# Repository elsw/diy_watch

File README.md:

# binary_watch

This is a project to create a homecrew binary watch to fit inside a analogue wrist watch

## issues

- No Vcc out of the LTC4071 chip, swapped LBSEL to set the `Low Battery Connect` to 3.6V but never get any voltage out. Change to MCP73833? also cheaper. [reference curcuit](https://learn.adafruit.com/li-ion-and-lipoly-batteries/downloads)
- Cannot debug RP2040 code, got it working once but not again, I think it's something up with the cdoe itself, debugging reliable blink code though... (change to pico 2??) (try embassy???)

## TODO

- Swap battery charger for MCP73833 (C340160)
- Recreate breadboard setup, test in rust
- Change PCB to 4 layer
- Change programming port for 3 pin JST SH (pico probe standard)
- Romove bool sel switch in favour of solder pads
- Swap LIR battery with space for lipo
- Add charging state LED
- Swap RTC for PCF-8563 (C2651526)

## Components
```
Cheap 6 digit LCD display
Raspberry Pi RP2040 Microchip
150mah lipo - https://thepihut.com/products/150mah-3-7v-lipo-battery
DS3231 real time clock
charging chip (breakout https://www.adafruit.com/product/259)
Standarise programming port on pico probe wire (1mm JST-SH, SM03B-SRSS-TB)
```

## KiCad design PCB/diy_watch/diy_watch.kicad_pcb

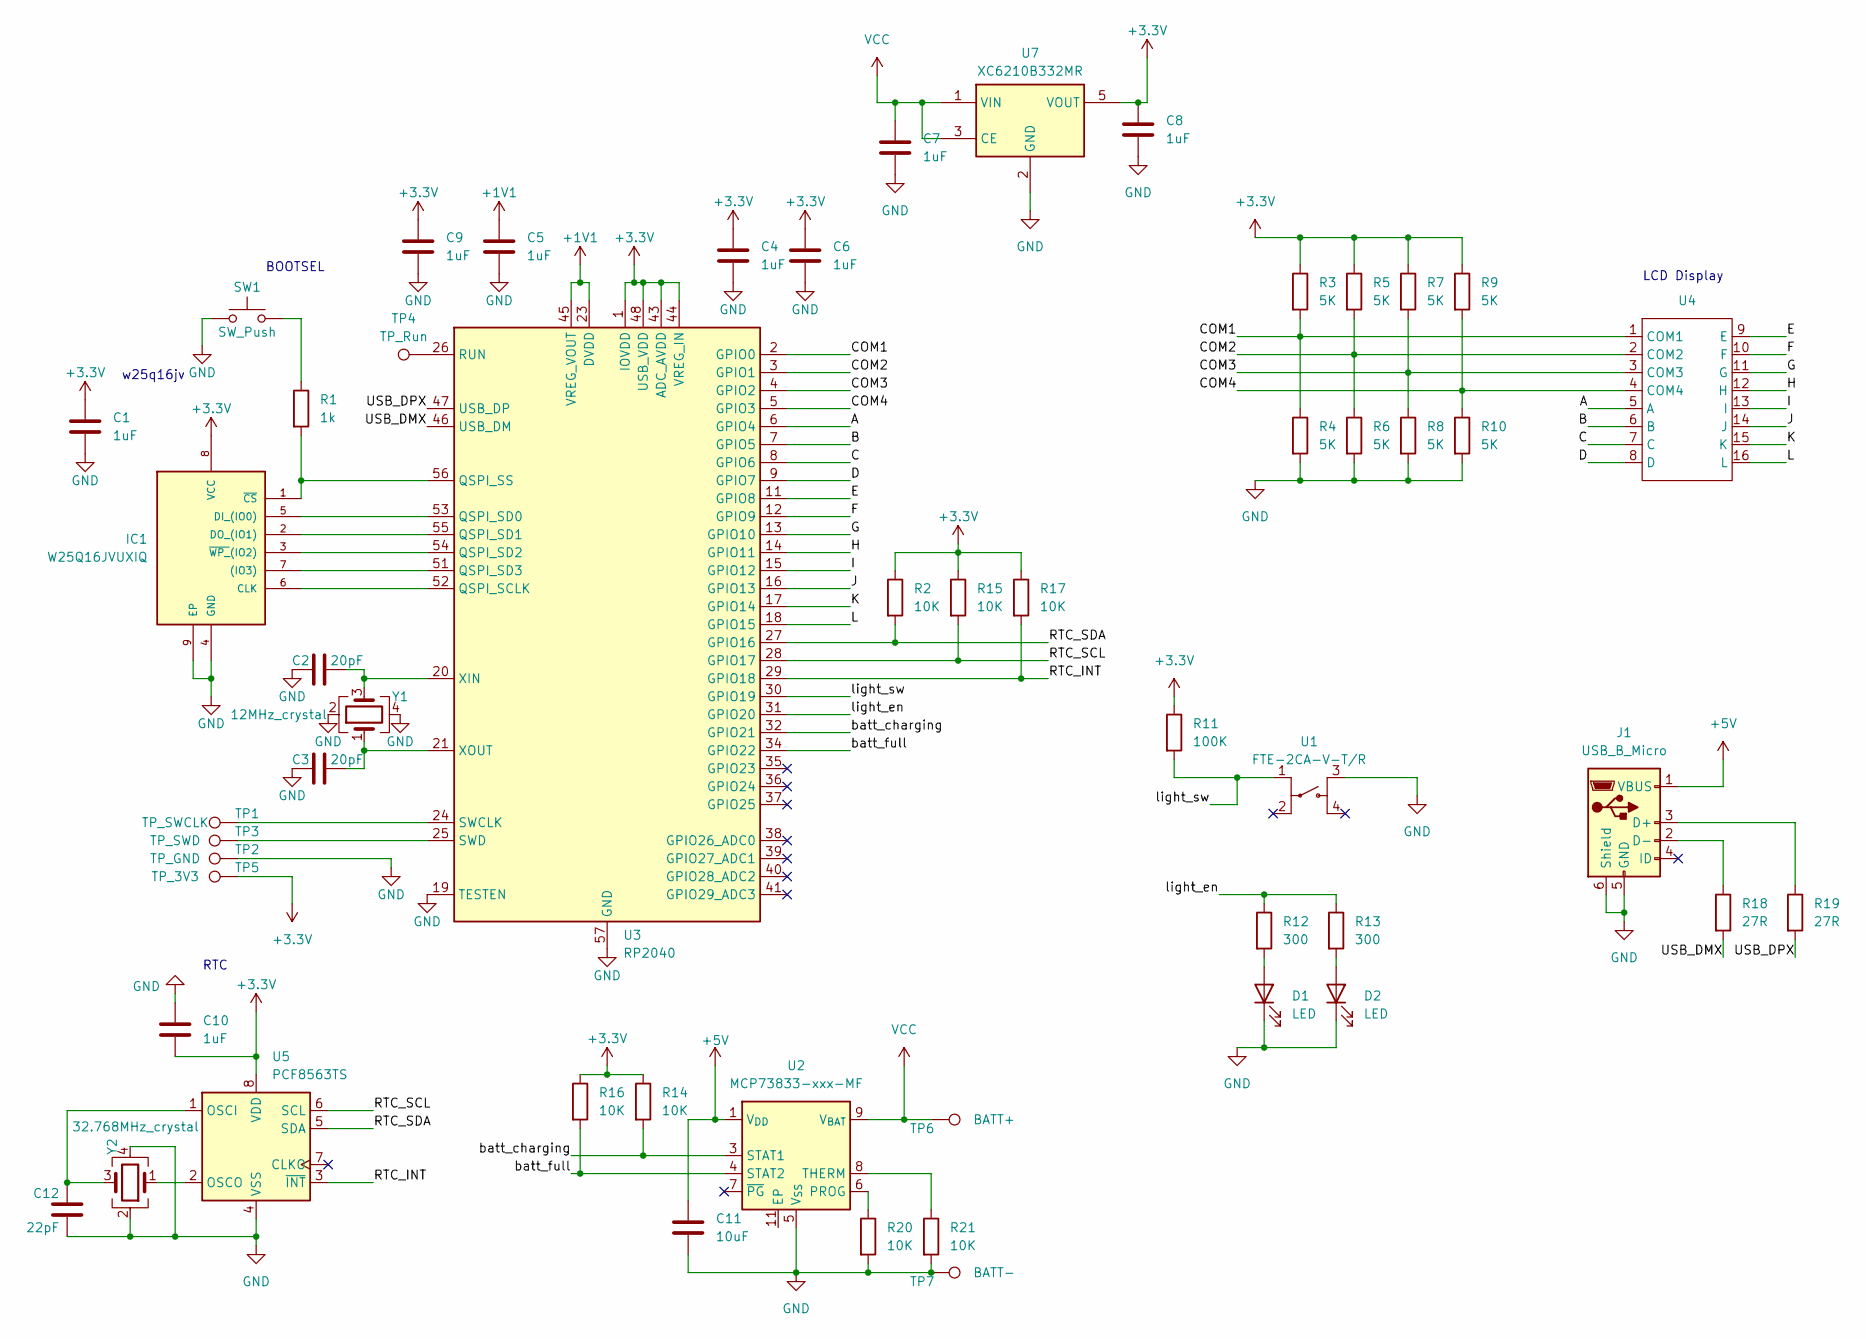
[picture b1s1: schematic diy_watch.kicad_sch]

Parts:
C1, C4, C5, C6, C7, C8, C9, C10: 1uF; C_0402_1005Metric; JLCPCB Part C52923
C2, C3: 20pF; C_0402_1005Metric; JLCPCB Part C1554
C11: 10uF; C_0402_1005Metric
C12: 22pF; C_0402_1005Metric
D1, D2: LED; LED_0805_2012Metric; JLCPCB Part C2296
IC1: W25Q16JVUXIQ; SON50P300X200X60-9N; MANUFACTURER_PART_NUMBER W25Q16JVUXIQ; JLCPCB Part C2843335
J1: USB_B_Micro; USB_Micro-B_GCT_USB3076-30-A
R1: 1k; R_0402_1005Metric; JLCPCB Part C11702
R2, R14, R15, R16, R17, R20, R21: 10K; R_0402_1005Metric; JLCPCB Part C25744
R3, R4, R5, R6, R7, R8, R9, R10: 5K; R_0402_1005Metric; JLCPCB Part C25900
R11: 100K; R_0402_1005Metric; JLCPCB Part C25741
R12: 300; R_0402_1005Metric; JLCPCB Part C25104
R13: 300; LED_0402_1005Metric; JLCPCB Part C25104
R18, R19: 27R; R_0402_1005Metric; JLCPCB Part C25100
SW1: SW_Push; SW_SPST_EVQP7C
TP1: TP_SWCLK; TestPoint_Pad_D1.5mm
TP2: TP_GND; TestPoint_Pad_D1.5mm
TP3: TP_SWD; TestPoint_Pad_D1.5mm
TP4: TP_Run; TestPoint_Pad_D1.0mm
TP5: TP_3V3; TestPoint_Pad_D1.5mm
TP6: BATT+; TestPoint_Pad_D1.5mm
TP7: BATT-; TestPoint_Pad_D1.5mm
U1: FTE-2CA-V-T/R; Diptronics FTE-3
U2: MCP73833-xxx-MF; DFN-10-1EP_3x3mm_P0.5mm_EP1.58x2.35mm
U3: RP2040; QFN-56-1EP_7x7mm_P0.4mm_EP3.2x3.2mm; JLCPCB Part C2040
U4: 6Dig7SegLCD
U5: PCF8563TS; MSOP-8_3x3mm_P0.65mm
U7: XC6210B332MR; SOT-23-5; JLCPCB Part C47719
Y1: 12MHz_crystal; Crystal_SMD_2520-4Pin_2.5x2.0mm; JLCPCB Part C252259
Y2: 32.768MHz_crystal; Crystal_SMD_2520-4Pin_2.5x2.0mm; JLCPCB Part C9002

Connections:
+1V1: C5.1, U3.23 (DVDD), U3.45 (VREG_VOUT), U3.50 (DVDD)
+3.3V: C1.1, C4.1, C6.1, C8.1, C9.1, C10.2, IC1.8 (VCC), R2.1, R3.1, R5.1, R7.1, R9.1, R11.1, R14.1, R15.1, R16.1, R17.1, TP5.1, U3.1 (IOVDD), U3.10 (IOVDD), U3.22 (IOVDD), U3.33 (IOVDD), U3.42 (IOVDD), U3.43 (ADC_AVDD), U3.44 (VREG_IN), U3.48 (USB_VDD), U3.49 (IOVDD), U5.8 (VDD), U7.5 (VOUT)
+5V: C11.1, J1.1 (VBUS), U2.1 (V_{DD}), U2.2 (V_{DD})
/A: U3.6 (GPIO4), U4.5 (A)
/B: U3.7 (GPIO5), U4.6 (B)
/C: U3.8 (GPIO6), U4.7 (C)
/COM1: R3.2, R4.1, U3.2 (GPIO0), U4.1 (COM1)
/COM2: R5.2, R6.1, U3.3 (GPIO1), U4.2 (COM2)
/COM3: R7.2, R8.1, U3.4 (GPIO2), U4.3 (COM3)
/COM4: R9.2, R10.1, U3.5 (GPIO3), U4.4 (COM4)
/D: U3.9 (GPIO7), U4.8 (D)
/E: U3.11 (GPIO8), U4.9 (E)
/F: U3.12 (GPIO9), U4.10 (F)
/G: U3.13 (GPIO10), U4.11 (G)
/H: U3.14 (GPIO11), U4.12 (H)
/I: U3.15 (GPIO12), U4.13 (I)
/J: U3.16 (GPIO13), U4.14 (J)
/K: U3.17 (GPIO14), U4.15 (K)
/L: U3.18 (GPIO15), U4.16 (L)
/RTC_INT: R17.2, U3.29 (GPIO18), U5.3 (~INT)
/RTC_SCL: R15.2, U3.28 (GPIO17), U5.6 (SCL)
/RTC_SDA: R2.2, U3.27 (GPIO16), U5.5 (SDA)
/USB_DMX: R18.2, U3.46 (USB_DM)
/USB_DPX: R19.2, U3.47 (USB_DP)
/batt_charging: R14.2, U2.3 (STAT1), U3.32 (GPIO21)
/batt_full: R16.2, U2.4 (STAT2), U3.34 (GPIO22)
/light_en: R12.1, R13.1, U3.31 (GPIO20)
/light_sw: R11.2, U1.1, U3.30 (GPIO19)
GND: C1.2, C2.1, C3.1, C4.2, C5.2, C6.2, C7.2, C8.2, C9.2, C10.1, C11.2, C12.1, D1.1 (K), D2.1 (K), IC1.4 (GND), IC1.9 (EP), J1.5 (GND), J1.6 (Shield), R4.2, R6.2, R8.2, R10.2, R20.2, R21.2, SW1.1, TP2.1, TP7.1, U1.3, U2.5 (V_{SS}), U3.19 (TESTEN), U3.57 (GND), U5.4 (VSS), U7.2 (GND), Y1.2, Y1.4, Y2.2, Y2.4
unnamed: D1.2 (A), R12.2
unnamed: D2.2 (A), R13.2
unnamed: IC1.7 ((IO3)), U3.51 (QSPI_SD3)
unnamed: IC1.6 (CLK), U3.52 (QSPI_SCLK)
unnamed: IC1.5 (DI_(IO0)), U3.53 (QSPI_SD0)
unnamed: IC1.2 (DO_(IO1)), U3.55 (QSPI_SD1)
unnamed: IC1.1 (~CS), R1.2, U3.56 (QSPI_SS)
unnamed: IC1.3 (~WP_(IO2)), U3.54 (QSPI_SD2)
unnamed: J1.3 (D+), R19.1
unnamed: J1.2 (D-), R18.1
unnamed: R1.1, SW1.2
unnamed: R20.1, U2.6 (PROG)
unnamed: R21.1, U2.8 (THERM)
unnamed: TP4.1, U3.26 (RUN)
unnamed: TP1.1, U3.24 (SWCLK)
unnamed: TP3.1, U3.25 (SWD)
unnamed: C2.2, U3.20 (XIN), Y1.3
unnamed: C3.2, U3.21 (XOUT), Y1.1
unnamed: C12.2, U5.1 (OSCI), Y2.3
unnamed: U5.2 (OSCO), Y2.1
VCC: C7.1, TP6.1, U2.9 (V_{BAT}), U2.10 (V_{BAT}), U7.1 (VIN), U7.3 (CE)

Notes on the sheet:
RTC
w25q16jv
BOOTSEL
LCD Display

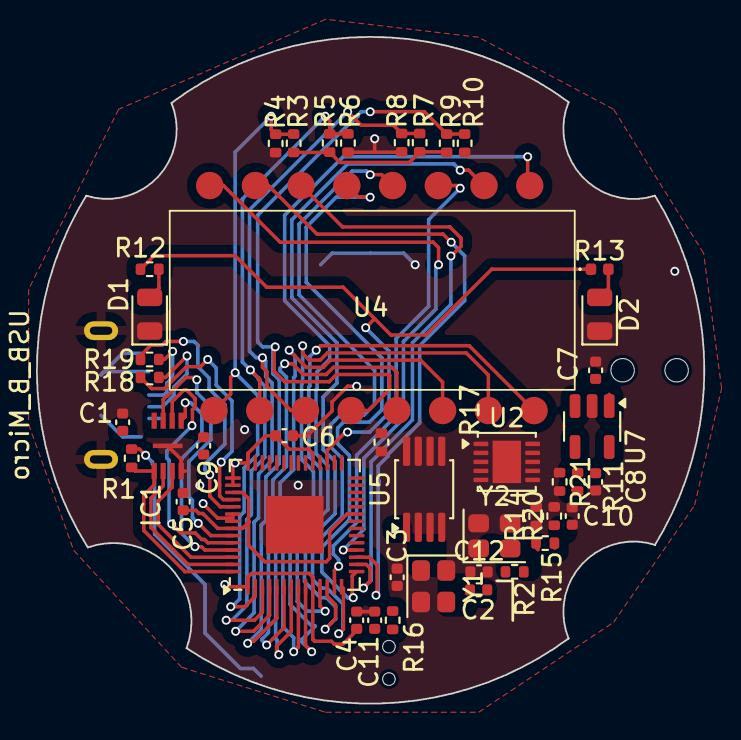
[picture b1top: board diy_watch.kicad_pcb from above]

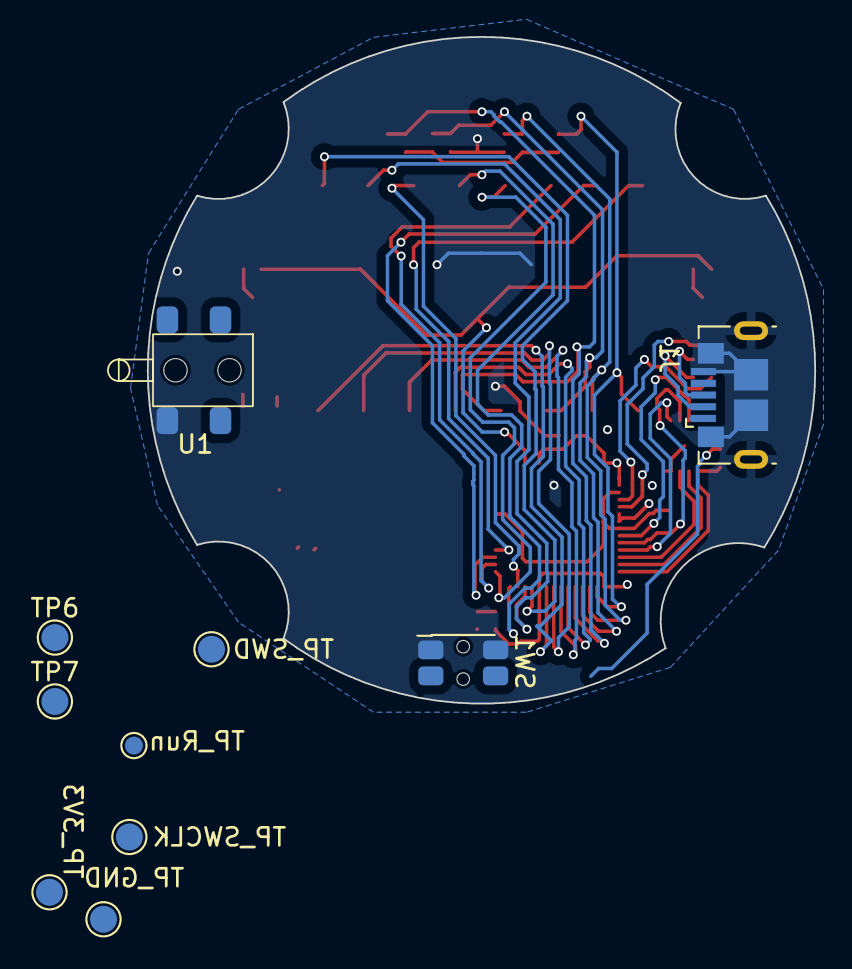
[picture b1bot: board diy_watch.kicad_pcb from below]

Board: 4 copper layers, 37.1 x 37.0 mm, 53 parts (10 on the bottom side), 50 nets.

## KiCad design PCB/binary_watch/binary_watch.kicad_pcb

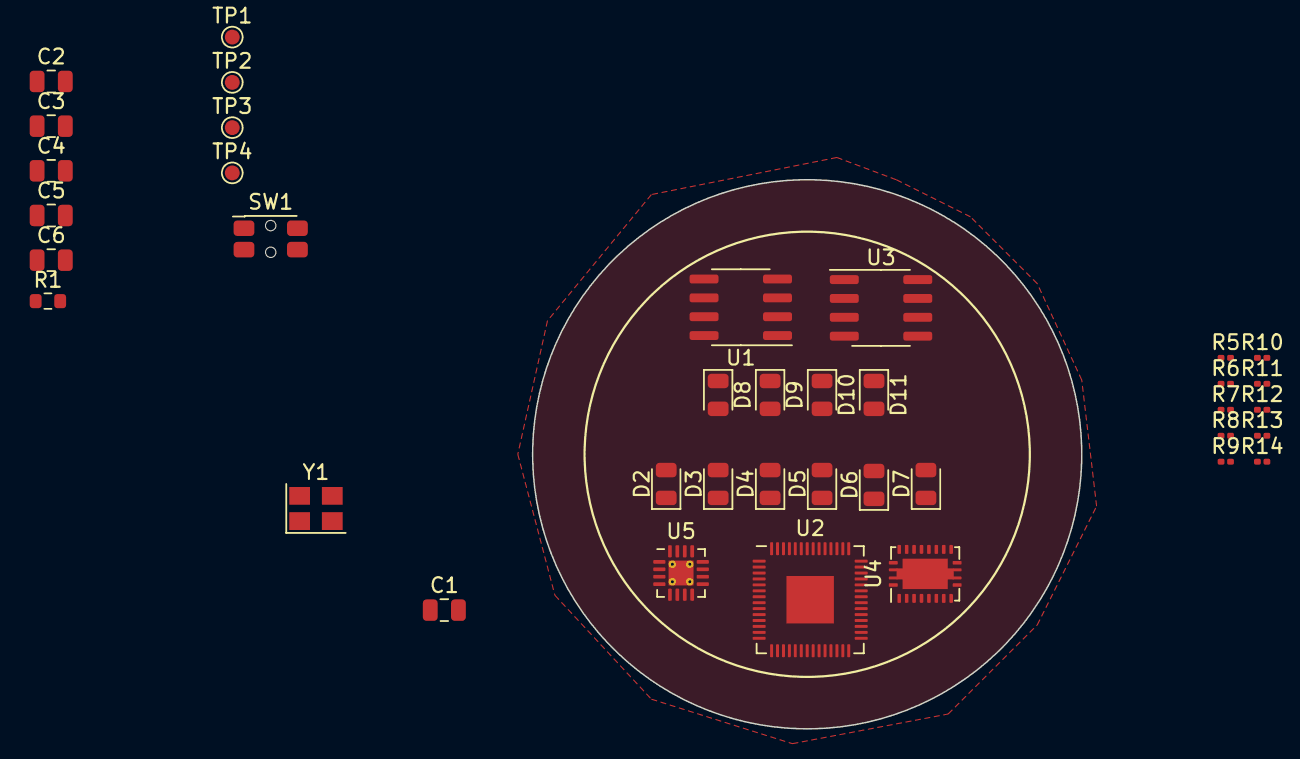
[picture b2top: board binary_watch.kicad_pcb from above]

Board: 2 copper layers, 37.0 x 37.0 mm, 39 parts (1 on the bottom side), 39 nets, no tracks yet.

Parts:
BT1: Battery_Cell; BatteryHolder_Multicomp_BC-2001_1x2032
C1, C4, C5, C6: 1uF; C_0805_2012Metric
C2, C3: 20pF; C_0805_2012Metric
D2, D3, D4, D5, D6, D7, D8, D9, D10, D11: LED; LED_0805_2012Metric
R1: 1k; R_0603_1608Metric
R5, R6, R7, R8, R9, R10, R11, R12, R13, R14: R175; R_0201_0603Metric
SW1: SW_Push; SW_SPST_EVQP7C
TP1, TP2, TP3, TP4: TestPoint; TestPoint_Pad_D1.0mm
U1: W25Q32JVSS; SOIC-8_3.9x4.9mm_P1.27mm
U2: RP2040; QFN-56-1EP_7x7mm_P0.4mm_EP3.2x3.2mm
U3: DS3231MZ; SOIC-8_3.9x4.9mm_P1.27mm
U4: BQ51050BRHL; Texas_VQFN-RHL-20
U5: BQ24230RGT; VQFN-16-1EP_3x3mm_P0.5mm_EP1.68x1.68mm_ThermalVias
Y1: 12MHz_crystal; Crystal_SMD_3225-4Pin_3.2x2.5mm

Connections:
+1V1: C4.1, U2.23 (DVDD), U2.45 (VREG_VOUT), U2.50 (DVDD)
+3.3V: C1.1, C5.1, C6.1, U1.8 (VCC), U2.1 (IOVDD), U2.10 (IOVDD), U2.22 (IOVDD), U2.33 (IOVDD), U2.42 (IOVDD), U2.43 (ADC_AVDD), U2.44 (VREG_IN), U2.48 (USB_VDD), U2.49 (IOVDD)
/ledH1: R14.1, U2.2 (GPIO0)
/ledH2: R13.1, U2.3 (GPIO1)
/ledH4: R12.1, U2.4 (GPIO2)
/ledH8: R11.1, U2.5 (GPIO3)
/ledM1: R10.1, U2.6 (GPIO4)
/ledM2: R9.1, U2.7 (GPIO5)
/ledM4: R8.1, U2.8 (GPIO6)
/ledM8: R7.1, U2.9 (GPIO7)
/ledM16: R6.1, U2.11 (GPIO8)
/ledM32: R5.1, U2.12 (GPIO9)
GND: BT1.2 (-), C1.2, C2.1, C3.1, C4.2, C5.2, C6.2, D2.1 (K), D3.1 (K), D4.1 (K), D5.1 (K), D6.1 (K), D7.1 (K), D8.1 (K), D9.1 (K), D10.1 (K), D11.1 (K), SW1.1, TP2.1, U1.4 (GND), U2.19 (TESTEN), U2.57 (GND), U4.1 (PGND), U4.9 (AD), U4.20 (PGND), U4.21 (PGND), Y1.2, Y1.4
unnamed: BT1.1 (+), U4.4 (BAT)
unnamed: D2.2 (A), R5.2
unnamed: D3.2 (A), R6.2
unnamed: D4.2 (A), R7.2
unnamed: D5.2 (A), R8.2
unnamed: D6.2 (A), R9.2
unnamed: D7.2 (A), R10.2
unnamed: D8.2 (A), R11.2
unnamed: D9.2 (A), R12.2
unnamed: D10.2 (A), R13.2
unnamed: D11.2 (A), R14.2
unnamed: R1.1, SW1.2
unnamed: U1.6 (CLK), U2.52 (QSPI_SCLK)
unnamed: U1.5 (DI(IO0)), U2.53 (QSPI_SD0)
unnamed: U1.2 (DO(IO1)), U2.55 (QSPI_SD1)
unnamed: U1.3 (IO2), U2.54 (QSPI_SD2)
unnamed: U1.7 (IO3), U2.51 (QSPI_SD3)
unnamed: R1.2, U1.1 (~CS), U2.56 (QSPI_SS)
unnamed: TP4.1, U2.26 (RUN)
unnamed: TP1.1, U2.24 (SWCLK)
unnamed: TP3.1, U2.25 (SWD)
unnamed: C2.2, U2.20 (XIN), Y1.3
unnamed: C3.2, U2.21 (XOUT), Y1.1
unnamed: U5.2 (BAT), U5.3 (BAT)
unnamed: U5.10 (OUT), U5.11 (OUT)
unnamed: U5.8 (VSS), U5.17 (VSS)

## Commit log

2023-11-18 Added PCB initial start
2023-11-19 Changed to use 7seg display, removing wireless charging
2023-11-21 Adding datasheets
2023-11-22 Added self contained test program for pico Added README for setup in WSL
2023-11-23 Updated READMEs
2023-11-23 Starting PIO driver to simplify lcd
2023-11-25 Adding LCD driver functionality Added LCD pinout picture
2023-11-26 Refactored to c++
2023-11-26 Adding windows instructions to README
2023-11-28 Updated README, added speed to launch command
2023-11-28 Fixing debugger
2023-12-06 Updating LCD driver Updated RTC pinout
2023-12-13 Refactoring LCD driver
2023-12-14 Fixed lcd driver inverted signals
2023-12-14 Fixed LCD digit matrix fixed LCD pin counts
2023-12-16 Added RTC clock output
2023-12-23 Adding USB serial communication Added python script to send time to the watch Moved i2c code to rtc constructor Added time counting to LCD
2023-12-23 Added dots to LCD output
2023-12-23 Updating watch PCB
    Added COM resistor pullup/downs
    Added switch
    Added LEDs
2023-12-23 Updated swich layout and symbol
2023-12-26 Routed most of the PCB, big staggetti
2023-12-27 Finished wiring, not started on DRC errors
2023-12-27 Added caps to regulator, Changed edge cut
    Adding missing pullup on switch
2023-12-27 Updated silkscreen names
2024-01-03 Removed wires and Rearranged PCB layout to create more space
2024-01-06 Changed charging chip and flash chip, rearranged parts
2024-01-07 Re-routed refactored board
2024-01-07 Fixing DRC errors on PCB
2024-01-18 Adding BOM
2024-01-18 Updating components for stock reasons
2024-02-17 Updated README with bugs found
2024-02-18 Adding usb data bug
2024-05-06 Adding fixes to PCB schematic
2025-02-19 Updating to 4 layer board Adding missing caps to schematic Updating pcb with schematic fixes
2025-02-19 Added more PCB tracks
2025-02-20 Refactored layer setup to be more efficient
2025-02-20 More routing on new 4 layer stack
2025-02-20 Fixing ERC and DRC errors
2025-02-25 Fixing DRC warnings
2025-02-25 Added mounting piont cutouts to PCB
2025-02-25 Rerouted with new spaces for back mounting
2025-02-26 More DRC corrections
2025-02-26 DRC Fixes
2025-02-27 More DRC fixes
2025-03-05 Adding JLC part numbers to schematic
2025-03-24 Updated cmake to use new VS code extension Updated readme to remove ubuntu & wsl instructions
2025-09-04 Fixed wrong number of digits, Added to README
2025-09-04 Added TODO list for new iteration
2025-09-05 Added tasks to README
2025-09-08 Adding rust refactor branch
2025-09-20 Adding probe-rs setup instructions
2025-09-20 Updating installation docs
2025-09-21 Adding template rust project for RP2040
2025-09-22 Adding start of pio support
2026-03-24 Adding DS3231 RTC to rust refactor
2026-04-02 Updating PCB with new RTC, charger, smaller ocillators
